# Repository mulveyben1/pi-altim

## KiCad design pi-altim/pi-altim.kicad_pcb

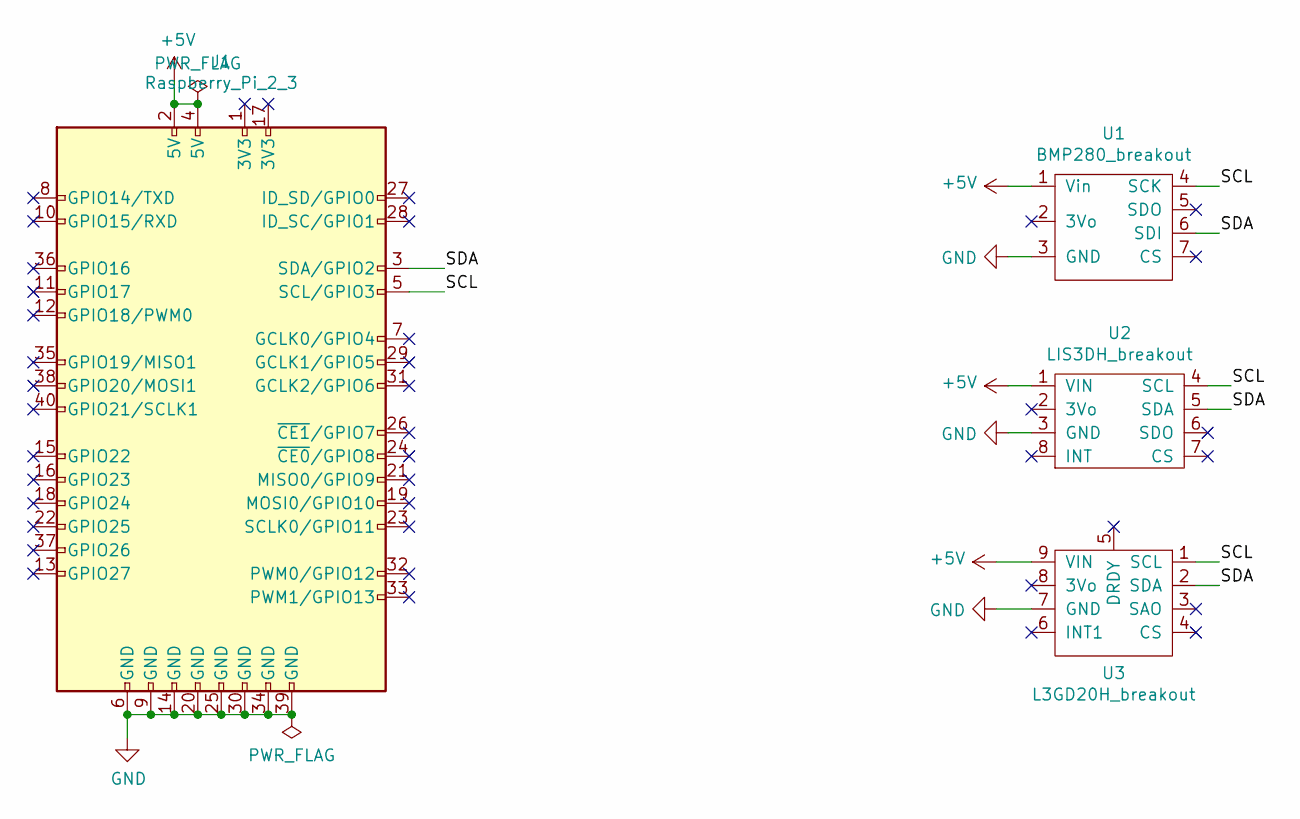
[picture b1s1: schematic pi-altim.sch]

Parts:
J1: Raspberry_Pi_2_3; Raspberry_Pi_Zero_Socketed_THT_FaceDown_MountingHoles
U1: BMP280_breakout; PinSocket_1x07_P2.54mm_Vertical
U2: LIS3DH_breakout; PinSocket_1x08_P2.54mm_Vertical
U3: L3GD20H_breakout; PinSocket_1x09_P2.54mm_Vertical

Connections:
+5V: J1.2 (5V), J1.4 (5V), U1.1 (Vin), U2.1 (VIN), U3.9 (VIN)
/SCL: J1.5 (SCL/GPIO3), U1.4 (SCK), U2.4 (SCL), U3.1 (SCL)
/SDA: J1.3 (SDA/GPIO2), U1.6 (SDI), U2.5 (SDA), U3.2 (SDA)
GND: J1.6 (GND), J1.9 (GND), J1.14 (GND), J1.20 (GND), J1.25 (GND), J1.30 (GND), J1.34 (GND), J1.39 (GND), U1.3 (GND), U2.3 (GND), U3.7 (GND)

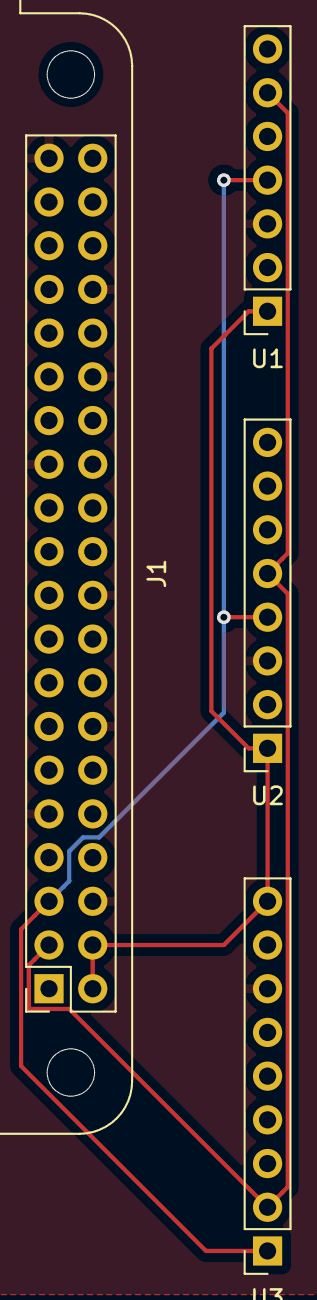
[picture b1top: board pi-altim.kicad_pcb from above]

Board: 2 copper layers, 4 parts (0 on the bottom side), 4 nets.

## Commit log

2019-02-27 add existing files
2019-12-28 pcb mount sensors & pi + gerbers
